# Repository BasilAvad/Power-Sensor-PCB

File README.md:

# Power-Sensor-PCB
Desgin PCB for Current and Voltage measurement

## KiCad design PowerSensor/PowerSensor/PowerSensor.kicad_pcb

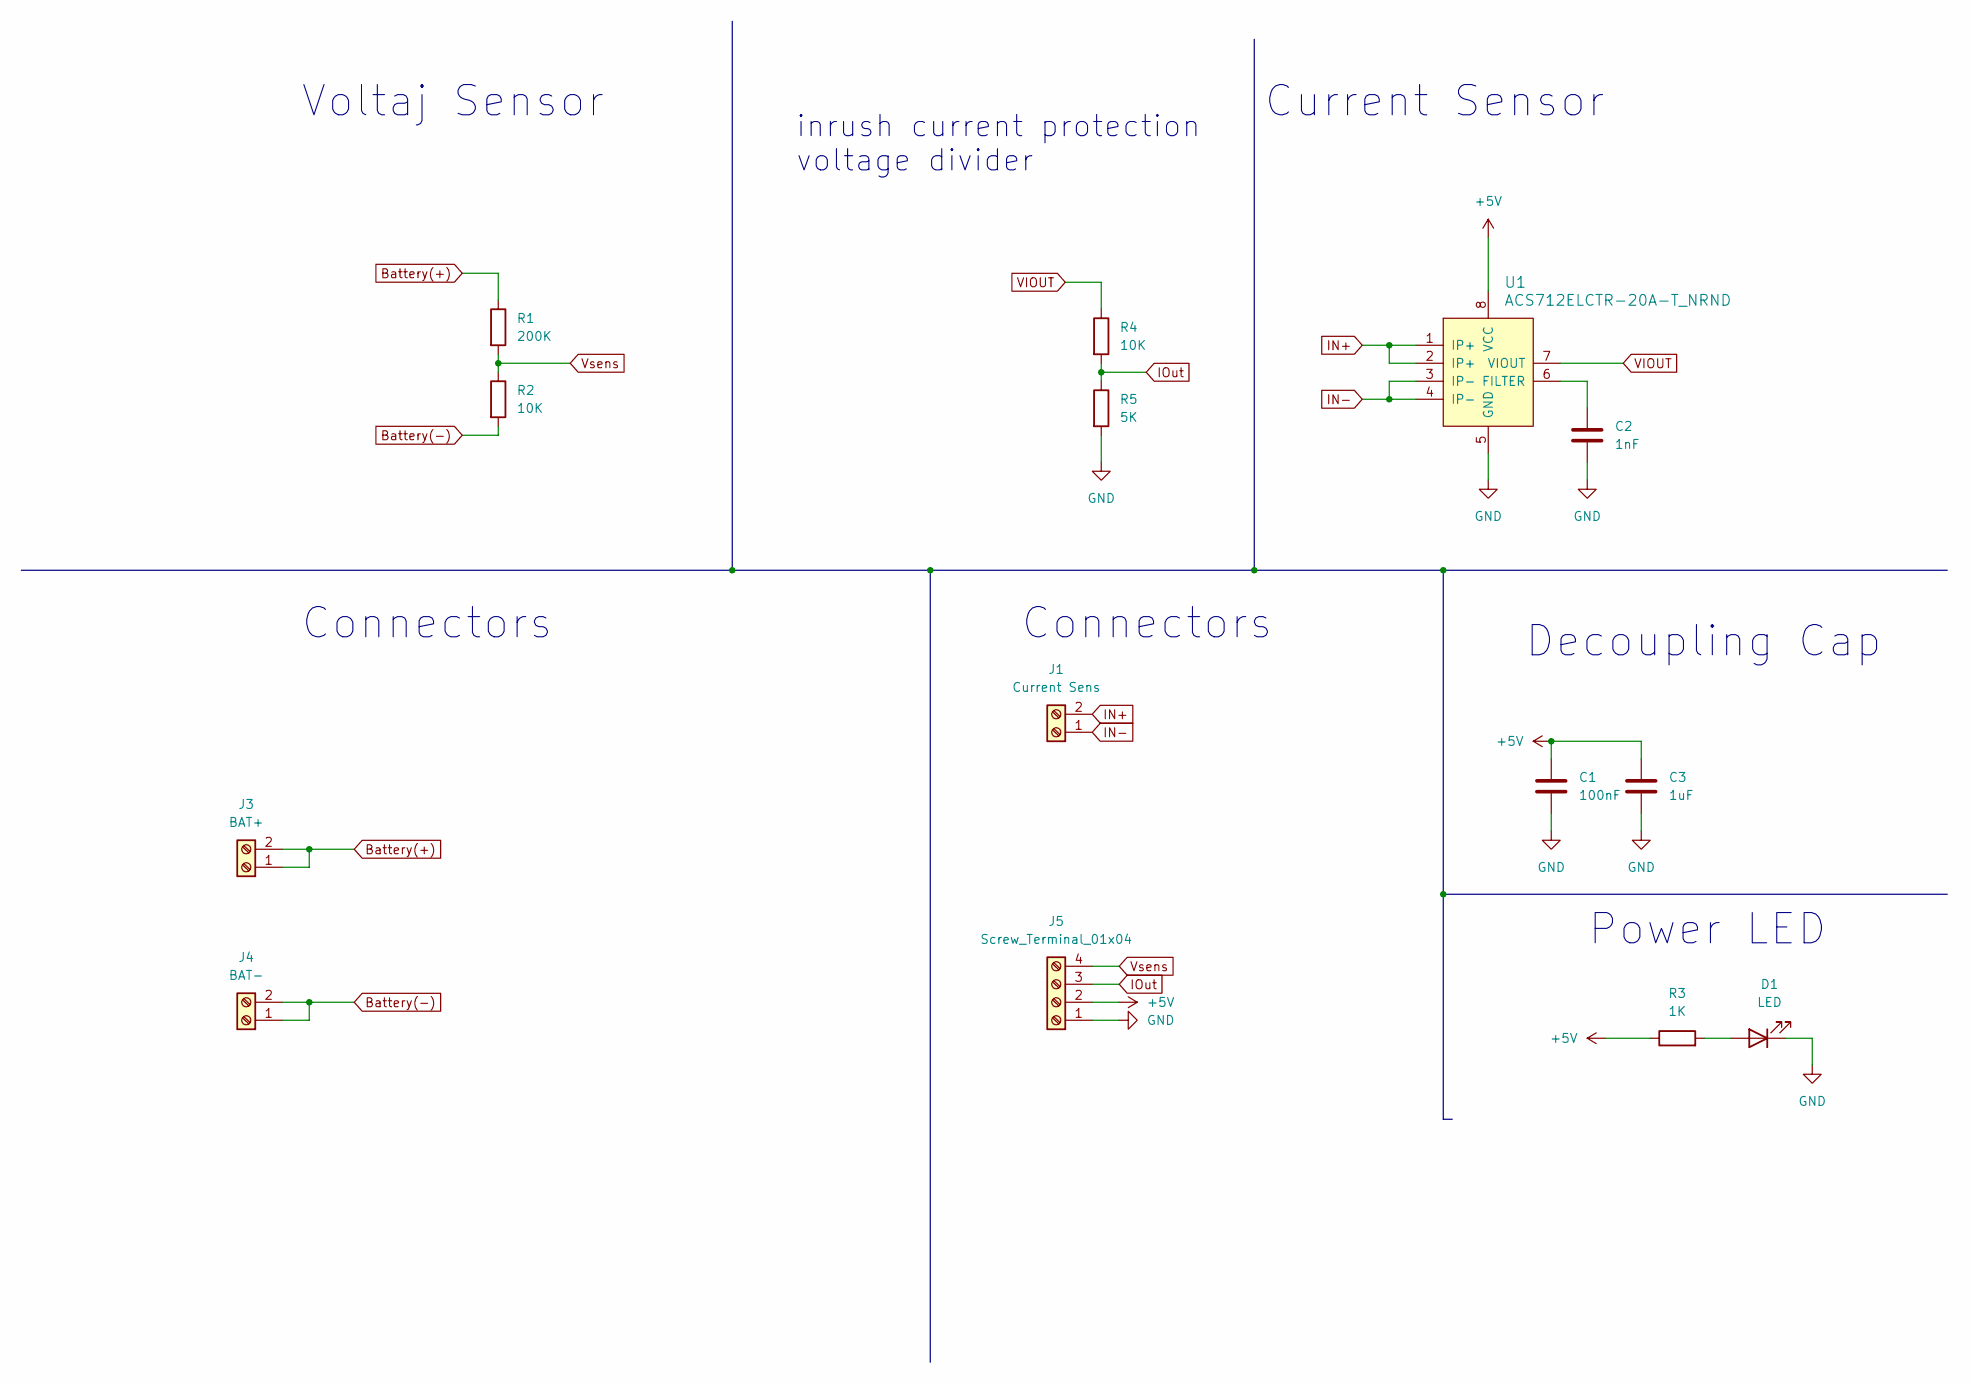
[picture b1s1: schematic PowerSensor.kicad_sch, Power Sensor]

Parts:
C1: 100nF; C_0805_2012Metric
C2: 1nF; C_0805_2012Metric
C3: 1uF; C_0805_2012Metric
D1: LED; LED_0805_2012Metric
J1: Current Sens; TerminalBlock_bornier-2_P5.08mm
J3: BAT+; TerminalBlock_bornier-2_P5.08mm
J4: BAT-; TerminalBlock_bornier-2_P5.08mm
J5: Screw_Terminal_01x04; TerminalBlock_bornier-4_P5.08mm
R1: 200K; R_0805_2012Metric
R2, R4: 10K; R_0805_2012Metric
R3: 1K; R_0805_2012Metric
R5: 5K; R_0805_2012Metric
U1: ACS712ELCTR-20A-T_NRND; SOIC-8_3.9x4.9mm_P1.27mm; MPN ACS712ELCTR-20A-T; Digi-Key_PN 620-1190-1-ND

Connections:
+5V: C1.1, C3.1, J5.2, R3.1, U1.8 (VCC)
Battery(+): J3.1, J3.2, R1.1
Battery(-): J4.1, J4.2, R2.2
GND: C1.2, C2.2, C3.2, D1.1 (K), J5.1, R5.2, U1.5 (GND)
IN+: J1.2, U1.1 (IP+), U1.2 (IP+)
IN-: J1.1, U1.3 (IP-), U1.4 (IP-)
IOut: J5.3, R4.2, R5.1
unnamed: D1.2 (A), R3.2
unnamed: C2.1, U1.6 (FILTER)
VIOUT: R4.1, U1.7 (VIOUT)
Vsens: J5.4, R1.2, R2.1

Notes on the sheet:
Connectors
Decoupling Cap
Power LED
inrush current protection voltage divider
Voltaj Sensor
Current Sensor

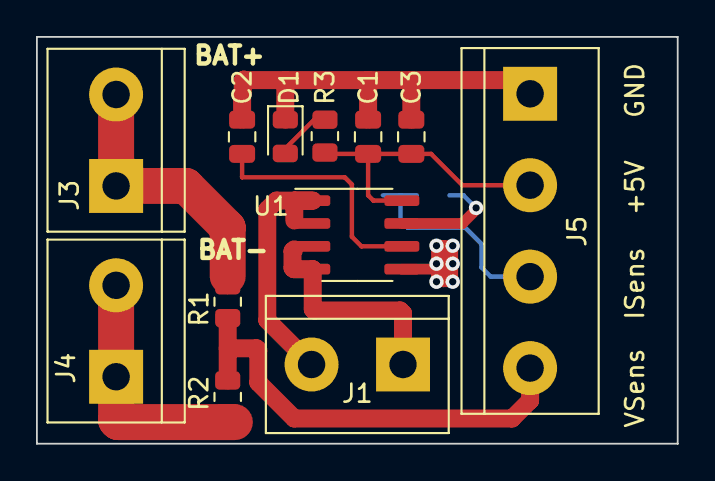
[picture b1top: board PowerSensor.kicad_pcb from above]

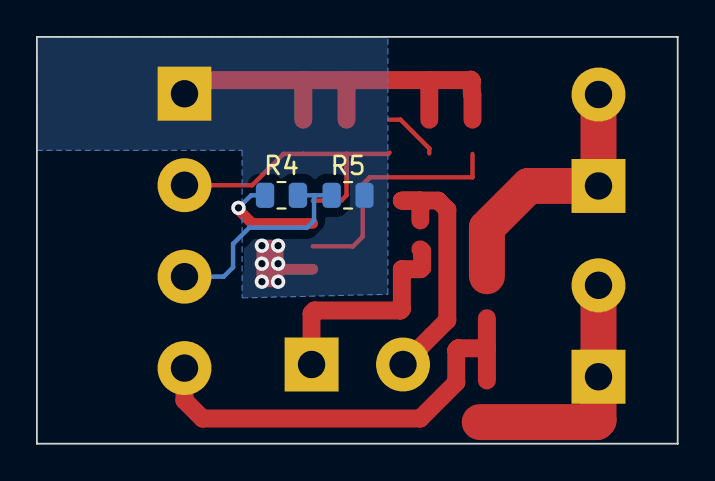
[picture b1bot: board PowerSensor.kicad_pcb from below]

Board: 2 copper layers, 35.6 x 22.6 mm, 14 parts (2 on the bottom side), 11 nets.

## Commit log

2023-12-25 First desgin of PCB version 0.1
2024-01-01 Change the main project with another project saved on desktop
2024-01-11 Add Decoupling Cap 1uF to 5V
2024-01-11 Add decupling Cap to 5V
2024-01-11 Re desgin PCB
2024-01-11 optimization for PCB
2024-01-12 PCB last optimization
2024-01-12 optimization
2024-01-12 PCB optimization 2
2024-01-12 Change the filter Cap value 1nF
2024-01-12 Optimization the desgin
2024-01-14 PCB optimozation
2024-01-31 Add voltage divider to current sensor output ( to Reduce Inrush Current)
2024-01-31 Change the voltage divider values
2024-01-31 Add the voltage divider into gesgin
2024-01-31 Optimize the desgin
2024-02-01 Remove the zip file from the project
2024-02-02 Update GND zone
2024-02-02 Add discription for voltage divider
2024-02-02 Add discription
2024-02-06 Optimize the routig on PCB
2024-03-30 Change the GND Plane in to solid and generete gerper file
2024-05-06 Some changes
